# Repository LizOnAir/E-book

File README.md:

# E-ink Devboard

This devboard is made to be a e-book that can connect to E-ink display, which make reading more easier and accessible.

## Features:
- low power consume rate
- read offline
- download books online
- no bluelight (YOU CAN READ BEFORE BED)

## CAD Model:

Made in Fusion360.Liz
Access files in [CAD folder](https://github.com/LizOnAir/E-book/tree/main/CAD).

## PCB
Here's my PCB! It was made in KiCad. 
### Schematic
Main board

E-ink Display

### PCB

Access files in [PCB folder](https://github.com/LizOnAir/E-book/tree/main/PCB).

## Firmware
I used Arduino IDE
Mode:
- download books
- add bookmark
- read

Access files in [Firmware folder](https://github.com/LizOnAir/E-book/tree/main/Firmware).

## BOM:
Here should be [everything](https://docs.google.com/spreadsheets/d/18-F1pZoXSL668FSytOyo6Q79A_xbLm0seJzbwmDT4q4/edit?gid=0#gid=0) you need to make this:
- 1x PCBA
- 1x 3.7V Lipo Battery 500mAh
- 1x Tactile buttons
- 1x 7.5 inch E-ink display
- 4x M3 14mm Screws
- 4x M3 OD4.2 L 4 Heatset inserts
- 1x 3d printed case

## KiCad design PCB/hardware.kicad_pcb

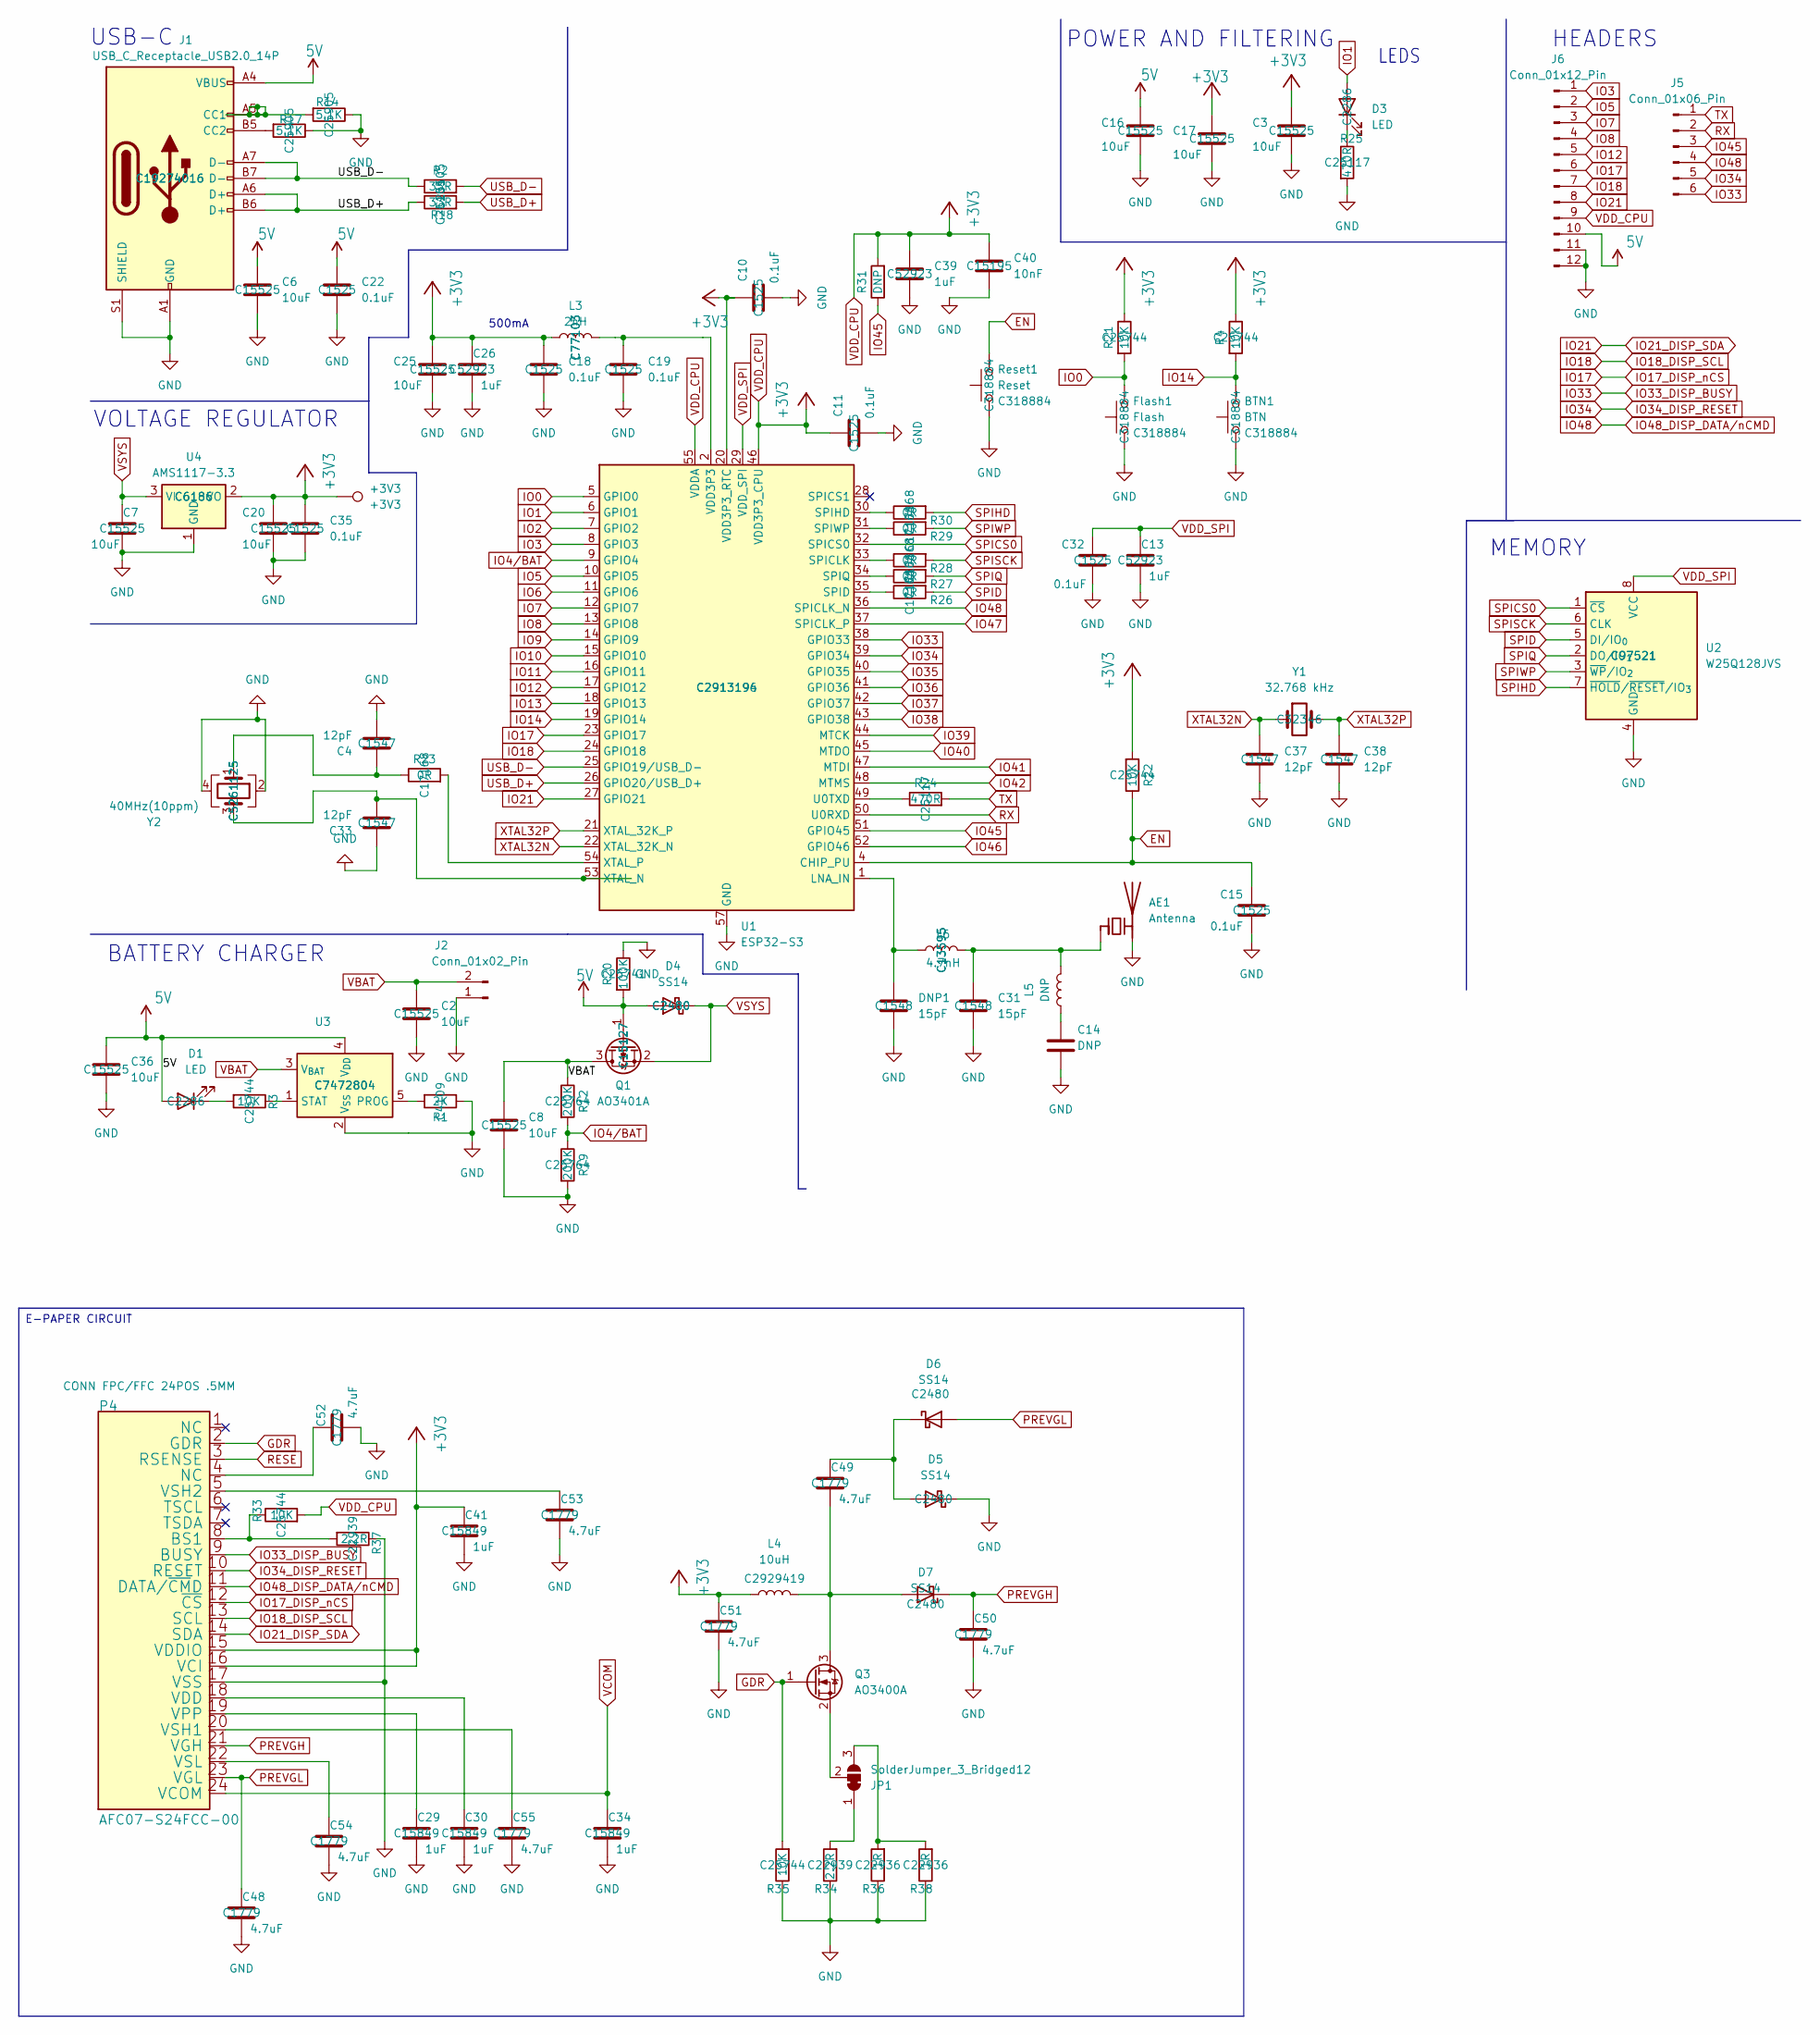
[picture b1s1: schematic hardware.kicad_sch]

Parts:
+3V3: +3V3; TestPoint_Pad_D1.0mm
AE1: Antenna; Texas_SWRA117D_2.4GHz_Left
BTN1: BTN; SW_Push_1P1T_XKB_TS-1187A; MNF PART NUMBER C318884; LCSC C318884
C2, C3, C6, C7, C8, C16, C17, C20, C25, C36: 10uF; C_0402_1005Metric; MNF PART NUMBER C15525; LCSC C15525
C4, C33, C37, C38: 12pF; C_0402_1005Metric; MNF PART NUMBER C1547; LCSC C1547
C10, C11, C15, C18, C19, C22, C32, C35: 0.1uF; C_0402_1005Metric; MNF PART NUMBER C1525; LCSC C1525
C13, C26, C39: 1uF; C_0402_1005Metric; MNF PART NUMBER C52923; LCSC C52923
C14: DNP; C_0402_1005Metric
C29, C30, C34, C41: 1uF; C_0603_1608Metric; MNF PART NUMBER C15849; LCSC C15849
C31: 15pF; C_0402_1005Metric; MNF PART NUMBER C1548; LCSC C1548
C40: 10nF; C_0402_1005Metric; MNF PART NUMBER C15195; LCSC C15195
C48, C49, C50, C51, C52, C53, C54, C55: 4.7uF; C_0805_2012Metric; MNF PART NUMBER C1779; LCSC C1779
D1, D3: LED; LED_0603_1608Metric; MNF PART NUMBER C2286; LCSC C2286
D4, D5, D6, D7: SS14; D_SMA; MNF PART NUMBER C2480; LCSC C2480
DNP1: 15pF; C_0402_1005Metric; MNF PART NUMBER C1548; LCSC C1548
Flash1: Flash; SW_Push_1P1T_XKB_TS-1187A; MNF PART NUMBER C318884; LCSC C318884
J1: USB_C_Receptacle_USB2.0_14P; USB_C_Receptacle_HCTL_HC-TYPE-C-16P-01A; MNF PART NUMBER C19274016; LCSC C19274016
J2: Conn_01x02_Pin; JST_PH_S2B-PH-K_1x02_P2.00mm_Horizontal
J5: Conn_01x06_Pin; PinHeader_1x06_P1.00mm_Vertical
J6: Conn_01x12_Pin; PinHeader_1x12_P1.00mm_Vertical
JP1: SolderJumper_3_Bridged12; SolderJumper-3_P1.3mm_Bridged12_RoundedPad1.0x1.5mm_NumberL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
L3: 2nH; L_0402_1005Metric; MNF PART NUMBER C77103; LCSC C77103
L4: 10uH; L_Ferrocore_DLG-0403; MNF PART NUMBER C2929419; LCSC C2929419
L5: DNP; L_0402_1005Metric
L6: 4.7nH; L_0402_1005Metric; MNF PART NUMBER C13595; LCSC C13595
P4: AFC07-S24FCC-00; Jushuo_AFC07-S24FCA-00_1x24-1MP_P0.50_Horizontal; MNF PART NUMBER C11057; LCSC C11057
Q1: AO3401A; SOT-23; MNF PART NUMBER C15127; LCSC C15127
Q3: AO3400A; SOT-23; MNF PART NUMBER C20917; LCSC C20917
R1: 2K; R_0402_1005Metric; MNF PART NUMBER C4109; LCSC C4109
R2, R18: 33R; R_0402_1005Metric; MNF PART NUMBER C25105; LCSC C25105
R3, R4, R21, R22, R33, R35: 10K; R_0402_1005Metric; MNF PART NUMBER C25744; LCSC C25744
R12, R19: 200K; R_0402_1005Metric; MNF PART NUMBER C25764; LCSC C25764
R14, R17: 5.1K; R_0402_1005Metric; MNF PART NUMBER C25905; LCSC C25905
R20: 100K; R_0402_1005Metric; MNF PART NUMBER C25741; LCSC C25741
R23, R26, R27, R28, R29, R30: 0R; R_0402_1005Metric; MNF PART NUMBER C17168; LCSC C17168
R24, R25: 470R; R_0402_1005Metric; MNF PART NUMBER C25117; LCSC C25117
R31: DNP; R_0402_1005Metric
R34, R37: 2.2R; R_0603_1608Metric; MNF PART NUMBER C22939; LCSC C22939
R36, R38: 1R; R_0603_1608Metric; MNF PART NUMBER C22936; LCSC C22936
Reset1: Reset; SW_Push_1P1T_XKB_TS-1187A; MNF PART NUMBER C318884; LCSC C318884
U1: ESP32-S3; QFN-56-1EP_7x7mm_P0.4mm_EP4x4mm; MNF PART NUMBER C2913196; LCSC C2913194
U2: W25Q128JVS; SOIC-8_5.3x5.3mm_P1.27mm; MNF PART NUMBER C97521; LCSC C97521
U3: MCP73831-2-OT; SOT-23-5; MNF PART NUMBER C7472804; LCSC C7472804
U4: AMS1117-3.3; SOT-223-3_TabPin2; MNF PART NUMBER C6186; LCSC C6186
Y1: 32.768 kHz; Crystal_SMD_3215-2Pin_3.2x1.5mm; MNF PART NUMBER C32346; LCSC C32346
Y2: 40MHz(10ppm); Crystal_SMD_2520-4Pin_2.5x2.0mm; MNF PART NUMBER C5261125; LCSC C5261125

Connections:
5V: C6.1, C16.1, C22.1, C36.1, D1.2 (A), D4.2 (A), J1.A4 (VBUS), J1.A9 (VBUS), J1.B4 (VBUS), J1.B9 (VBUS), J6.10, Q1.1 (G), R20.2, U3.4 (V_{DD})
EN: C15.1, R22.1, Reset1.2, U1.4 (CHIP_PU)
GDR: P4.2 (GDR), Q3.1 (G), R35.2
GND: AE1.2 (PCB_Trace), BTN1.1, C2.2, C3.2, C4.2, C6.2, C7.2, C8.2, C10.2, C11.2, C13.2, C14.2, C15.2, C16.2, C17.2, C18.2, C19.2, C20.2, C22.2, C25.2, C26.2, C29.2, C30.2, C31.2, C32.2, C33.1, C34.2, C35.2, C36.2, C37.2, C38.2, C39.2, C40.2, C41.2, C48.2, C50.2, C51.2, C52.2, C53.2, C54.2, C55.2, D5.1 (K), DNP1.2, Flash1.1, J1.A1 (GND), J1.A12 (GND), J1.B1 (GND), J1.B12 (GND), J1.S1 (SHIELD), J2.1, J6.11, J6.12, P4.17 (VSS), R1.1, R14.1, R17.1, R19.2, R20.1, R25.2, R34.1, R35.1, R36.1, R37.1, R38.1, Reset1.1, U1.57 (GND), U2.4 (GND), U3.2 (V_{SS}), U4.1 (GND), Y2.2, Y2.4
IO0: Flash1.2, R21.2, U1.5 (GPIO0)
IO1: D3.2 (A), U1.6 (GPIO1)
IO2: U1.7 (GPIO2)
IO3: J6.1, U1.8 (GPIO3)
IO4/BAT: R12.2, R19.1, U1.9 (GPIO4)
IO5: J6.2, U1.10 (GPIO5)
IO6: U1.11 (GPIO6)
IO7: J6.3, U1.12 (GPIO7)
IO8: J6.4, U1.13 (GPIO8)
IO9: U1.14 (GPIO9)
IO10: U1.15 (GPIO10)
IO11: U1.16 (GPIO11)
IO12: J6.5, U1.17 (GPIO12)
IO13: U1.18 (GPIO13)
IO14: BTN1.2, R4.2, U1.19 (GPIO14)
IO17: J6.6, P4.12 (~CS), U1.23 (GPIO17)
IO18: J6.7, P4.13 (SCL), U1.24 (GPIO18)
IO21: J6.8, P4.14 (SDA), U1.27 (GPIO21)
IO33: J5.6, P4.9 (BUSY), U1.38 (GPIO33)
IO34: J5.5, P4.10 (RESET), U1.39 (GPIO34)
IO35: U1.40 (GPIO35)
IO36: U1.41 (GPIO36)
IO37: U1.42 (GPIO37)
IO38: U1.43 (GPIO38)
IO39: U1.44 (MTCK)
IO40: U1.45 (MTDO)
IO41: U1.47 (MTDI)
IO42: U1.48 (MTMS)
IO45: J5.3, R31.1, U1.51 (GPIO45)
IO46: U1.52 (GPIO46)
IO47: U1.37 (SPICLK_P)
IO48: J5.4, P4.11 (DATA/~CMD), U1.36 (SPICLK_N)
unnamed: AE1.1 (FEED), C31.1, L5.2, L6.2
unnamed: C4.1, R23.1, Y2.1
unnamed: C14.1, L5.1
unnamed: C19.1, L3.2, U1.2 (VDD3P3), U1.3 (VDD3P3)
unnamed: C52.1, P4.4 (NC)
unnamed: D1.1 (K), R3.2
unnamed: D3.1 (K), R25.1
unnamed: C49.1, D5.2 (A), D6.1 (K)
unnamed: C49.2, D7.2 (A), L4.2, Q3.3 (D)
unnamed: J1.A5 (CC1), R14.2
unnamed: J1.B5 (CC2), R17.2
unnamed: JP1.1 (A), R34.2
unnamed: JP1.3 (B), R36.2, R38.2
unnamed: JP1.2 (C), Q3.2 (S)
unnamed: P4.8 (BS1), R33.1, R37.2
unnamed: C30.1, P4.18 (VDD)
unnamed: C29.1, P4.19 (VPP)
unnamed: C55.1, P4.20 (VSH1)
unnamed: C53.1, P4.5 (VSH2)
unnamed: C54.1, P4.22 (VSL)
unnamed: DNP1.1, L6.1, U1.1 (LNA_IN)
unnamed: R28.1, U1.33 (SPICLK)
unnamed: R26.1, U1.35 (SPID)
unnamed: R30.1, U1.30 (SPIHD)
unnamed: R27.1, U1.34 (SPIQ)
unnamed: R29.1, U1.31 (SPIWP)
unnamed: R24.1, U1.49 (U0TXD)
unnamed: C33.2, U1.53 (XTAL_N), Y2.3
unnamed: R23.2, U1.54 (XTAL_P)
unnamed: R1.2, U3.5 (PROG)
unnamed: R3.1, U3.1 (STAT)
PREVGH: C50.1, D7.1 (K), P4.21 (VGH)
PREVGL: C48.1, D6.2 (A), P4.23 (VGL)
RESE: P4.3 (RSENSE)
RX: J5.2, U1.50 (U0RXD)
SPICS0: U1.32 (SPICS0), U2.1 (~CS)
SPID: R26.2, U2.5 (DI/IO_{0})
SPIHD: R30.2, U2.7 (~HOLD/~RESET/IO_{3})
SPIQ: R27.2, U2.2 (DO/IO_{1})
SPISCK: R28.2, U2.6 (CLK)
SPIWP: R29.2, U2.3 (~WP/IO_{2})
TX: J5.1, R24.2
USB_D+: J1.A6 (D+), J1.B6 (D+), R18.1, R18.2, U1.26 (GPIO20/USB_D+)
USB_D-: J1.A7 (D-), J1.B7 (D-), R2.1, R2.2, U1.25 (GPIO19/USB_D-)
VBAT: C2.1, C8.1, J2.2, Q1.3 (D), R12.1, U3.3 (V_{BAT})
VCOM: C34.1, P4.24 (VCOM)
VDD_CPU: +3V3.1, C3.1, C10.1, C11.1, C17.1, C18.1, C20.1, C25.1, C26.1, C35.1, C39.1, C40.1, C41.1, C51.1, J6.9, L3.1, L4.1, P4.15 (VDDIO), P4.16 (VCI), R4.1, R21.1, R22.2, R31.2, R33.2, U1.20 (VDD3P3_RTC), U1.46 (VDD3P3_CPU), U1.55 (VDDA), U1.56 (VDDA), U4.2 (VO)
VDD_SPI: C13.1, C32.1, U1.29 (VDD_SPI), U2.8 (VCC)
VSYS: C7.1, D4.1 (K), Q1.2 (S), U4.3 (VI)
XTAL32N: C37.1, U1.22 (XTAL_32K_N), Y1.1
XTAL32P: C38.1, U1.21 (XTAL_32K_P), Y1.2

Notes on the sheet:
500mA
BATTERY CHARGER
VOLTAGE REGULATOR
LEDS
HEADERS
MEMORY
POWER AND FILTERING
USB-C
E-PAPER CIRCUIT

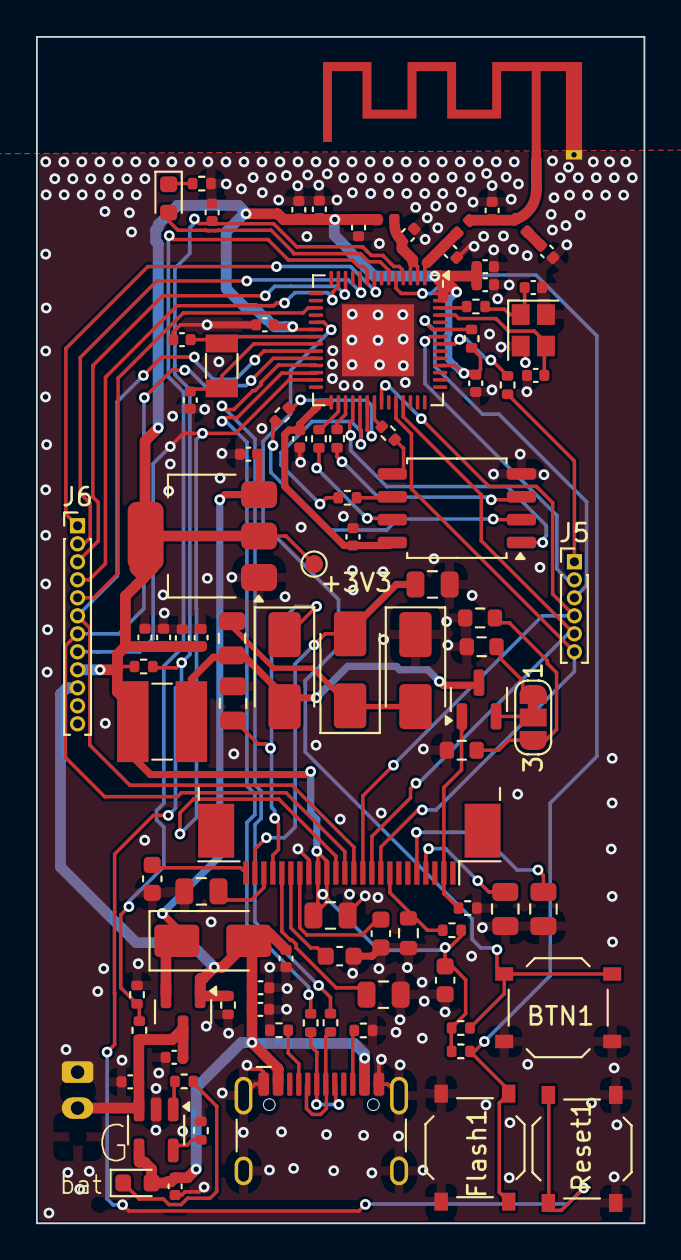
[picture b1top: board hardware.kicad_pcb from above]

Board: 2 copper layers, 33.8 x 65.9 mm, 97 parts (1 on the bottom side), 70 nets.

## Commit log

2026-05-18 Rename hardware.kicad_pro to PCB/hardware.kicad_pro
2026-05-19 Create CAD
2026-05-19 Rename E-inkPCB.step to CAD/E-inkPCB.step
